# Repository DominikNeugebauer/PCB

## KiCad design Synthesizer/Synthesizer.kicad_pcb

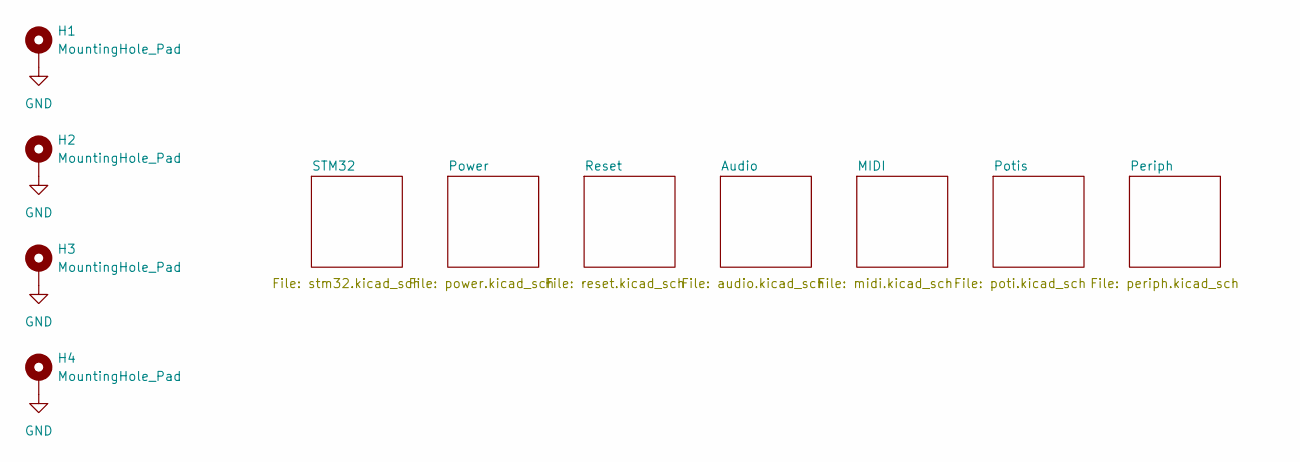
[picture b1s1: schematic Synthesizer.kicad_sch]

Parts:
H1, H2, H3, H4: MountingHole_Pad; MountingHole_5.3mm_M5_DIN965_Pad

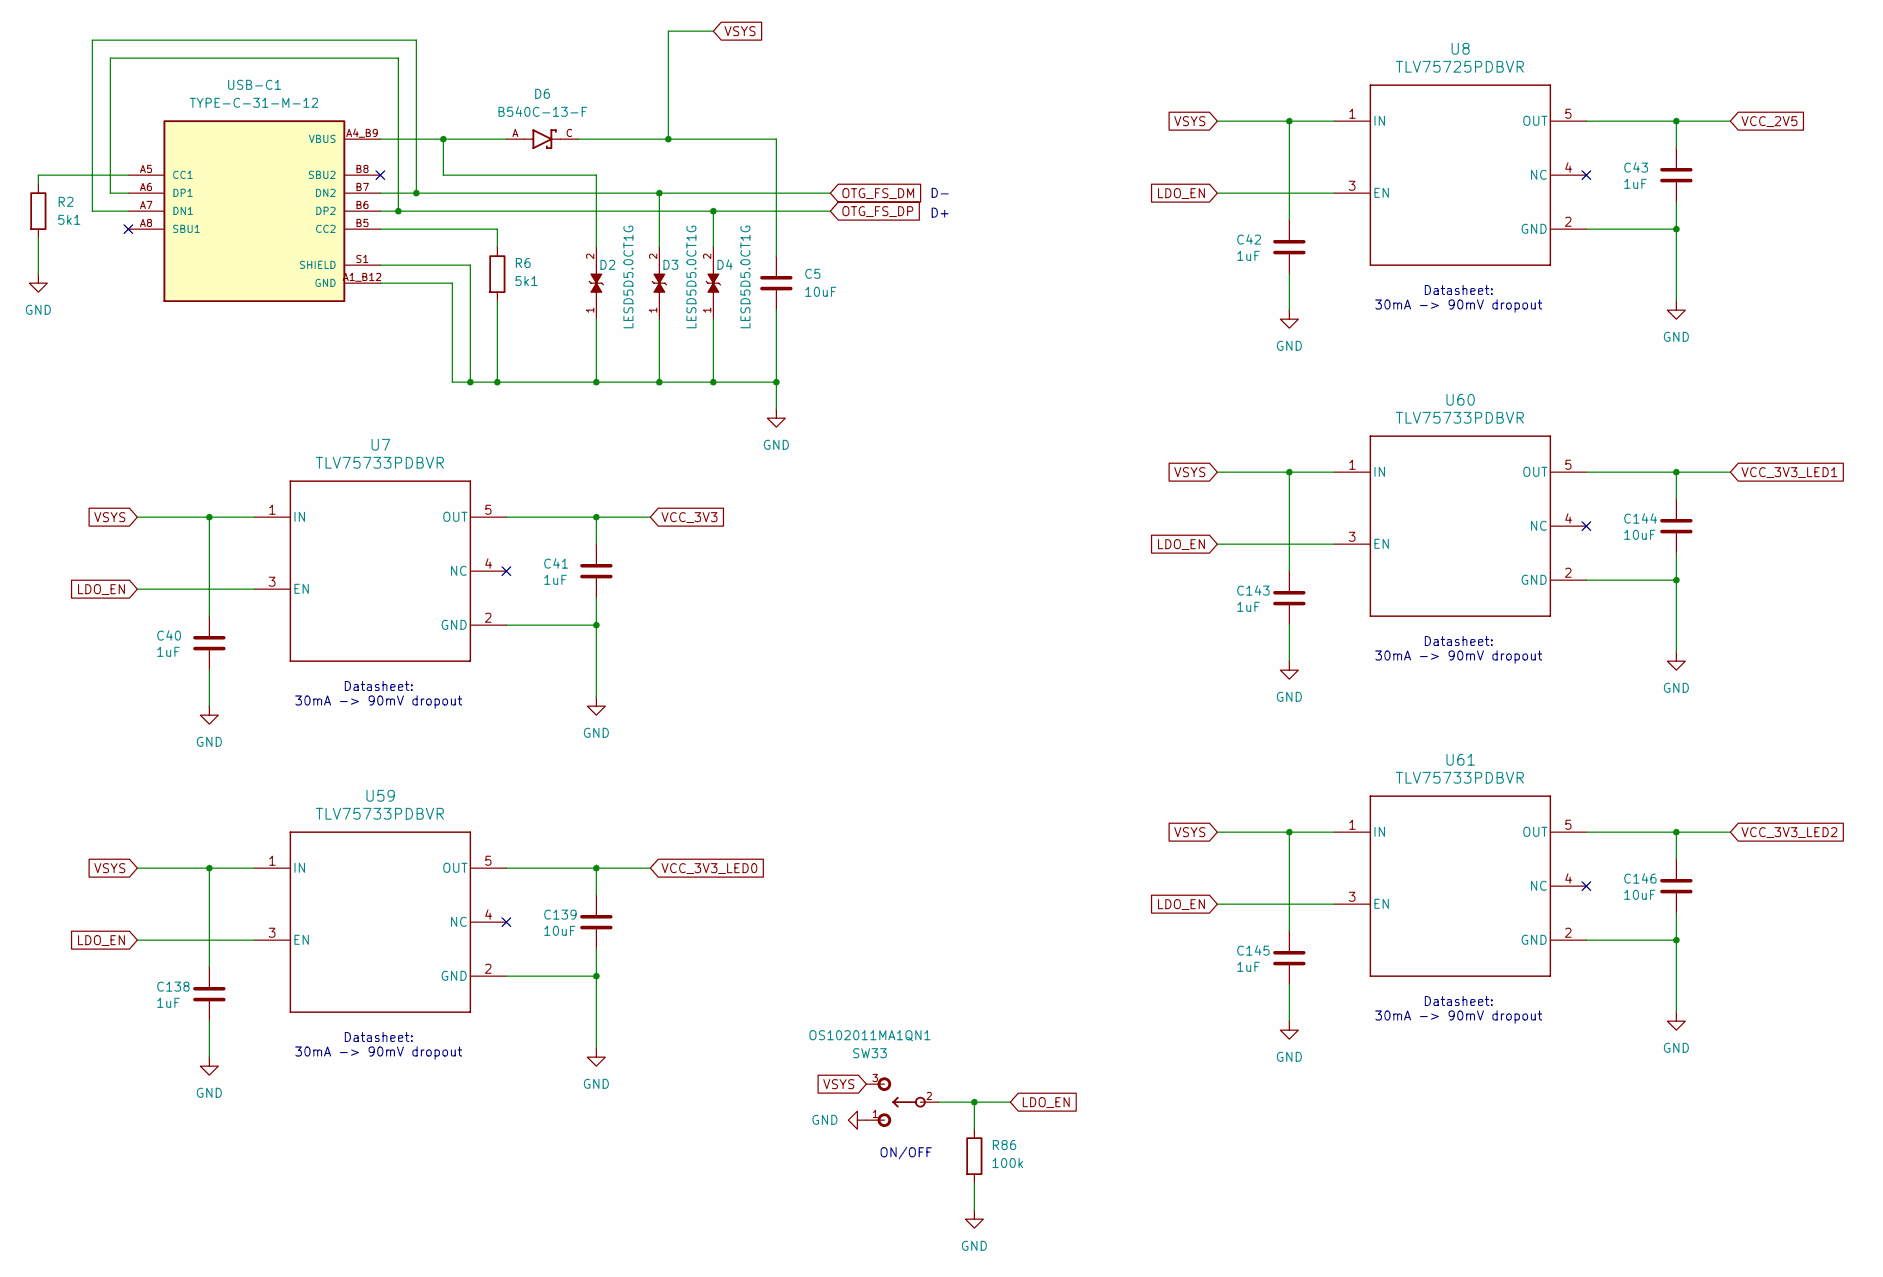
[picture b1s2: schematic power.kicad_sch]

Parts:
C5, C139, C144, C146: 10uF; C_0603_1608Metric
C40, C41, C42, C43, C138, C143, C145: 1uF; C_0603_1608Metric
D2, D3, D4: LESD5D5.0CT1G; TVS_LESD5D5.0CT1G; PARTREV O
D6: B540C-13-F; MPN B540C-13-F
R2, R6: 5k1; R_0603_1608Metric
R86: 100k; R_0603_1608Metric
SW33: OS102011MA1QN1; SWITCH_OS102011MA1QN1_SWITCH_11MA1QN1; MANUFACTURER_PART_NUMBER OS102011MA1QN1
U7, U59, U60, U61: TLV75733PDBVR; SOT-23-5
U8: TLV75725PDBVR; SOT-23-5
USB-C1: TYPE-C-31-M-12; USBC_HRO_TYPE-C-31-M-12; PARTREV 2020.12.08

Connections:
LDO_EN: R86.1, SW33.2, U7.3 (EN), U8.3 (EN), U59.3 (EN), U60.3 (EN), U61.3 (EN)
unnamed: R2.1, USB-C1.A5 (CC1)
unnamed: R6.1, USB-C1.B5 (CC2)
OTG_FS_DM: D3.2, USB-C1.A7 (DN1), USB-C1.B7 (DN2); also elsewhere on the board
OTG_FS_DP: D4.2, USB-C1.A6 (DP1), USB-C1.B6 (DP2); also elsewhere on the board
VBUS: D2.2, D6.A, USB-C1.A4_B9 (VBUS), USB-C1.B4_A9 (VBUS)
VCC_2V5: C43.1, U8.5 (OUT); also elsewhere on the board
VCC_3V3: C41.1, U7.5 (OUT); also elsewhere on the board
VCC_3V3_LED0: C139.1, U59.5 (OUT); also elsewhere on the board
VCC_3V3_LED1: C144.1, U60.5 (OUT); also elsewhere on the board
VCC_3V3_LED2: C146.1, U61.5 (OUT); also elsewhere on the board
VSYS: C5.1, C40.1, C42.1, C138.1, C143.1, C145.1, D6.C, SW33.3, U7.1 (IN), U8.1 (IN), U59.1 (IN), U60.1 (IN), U61.1 (IN)

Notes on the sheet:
Datasheet: 30mA -> 90mV dropout
ON/OFF

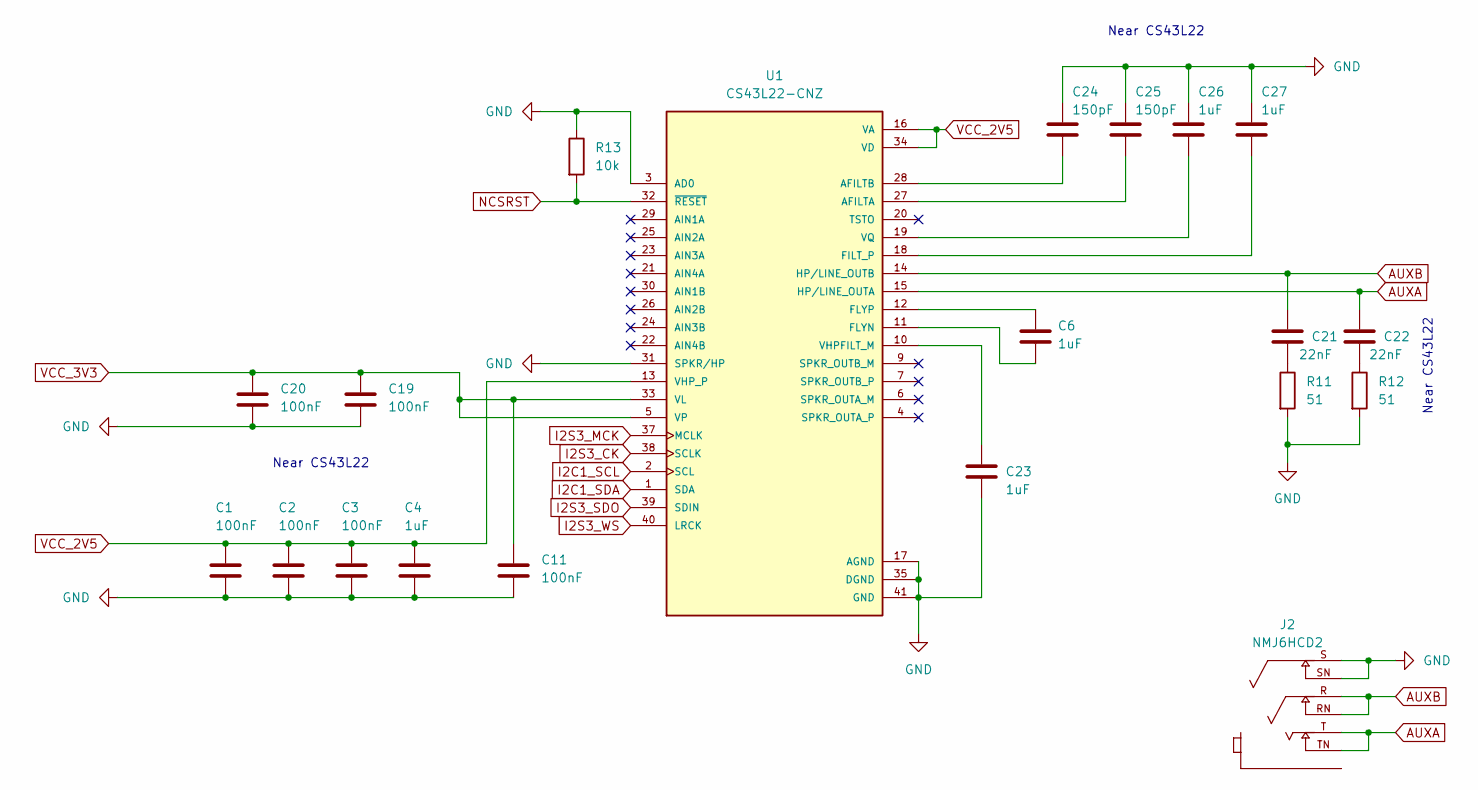
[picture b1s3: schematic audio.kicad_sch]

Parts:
C1, C2, C3, C11, C19, C20: 100nF; C_0603_1608Metric
C4, C6, C23, C26, C27: 1uF; C_0603_1608Metric
C21, C22: 22nF; C_0603_1608Metric
C24, C25: 150pF; C_0603_1608Metric
J2: NMJ6HCD2; AUXBIG_NEUTRIK_NMJ6HCD2; PARTREV 26.02.2021
R11, R12: 51; R_0603_1608Metric
R13: 10k; R_0603_1608Metric
U1: CS43L22-CNZ; CS43L22; PARTREV F2

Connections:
AUXA: C22.1, J2.T, J2.TN, U1.15 (HP/LINE_OUTA)
AUXB: C21.1, J2.R, J2.RN, U1.14 (HP/LINE_OUTB)
I2C1_SCL: U1.2 (SCL); also elsewhere on the board
I2C1_SDA: U1.1 (SDA); also elsewhere on the board
I2S3_CK: U1.38 (SCLK); also elsewhere on the board
I2S3_MCK: U1.37 (MCLK); also elsewhere on the board
I2S3_SDO: U1.39 (SDIN); also elsewhere on the board
I2S3_WS: U1.40 (LRCK); also elsewhere on the board
NCSRST: R13.2, U1.32 (~RESET); also elsewhere on the board
unnamed: C21.2, R11.1
unnamed: C22.2, R12.1
unnamed: C25.2, U1.27 (AFILTA)
unnamed: C24.2, U1.28 (AFILTB)
unnamed: C27.2, U1.18 (FILT_P)
unnamed: C6.2, U1.11 (FLYN)
unnamed: C6.1, U1.12 (FLYP)
unnamed: C23.1, U1.10 (VHPFILT_M)
unnamed: C26.2, U1.19 (VQ)
VCC_2V5: C1.1, C2.1, C3.1, C4.1, U1.13 (VHP_P), U1.16 (VA), U1.34 (VD); also elsewhere on the board
VCC_3V3: C11.1, C19.1, C20.1, U1.5 (VP), U1.8 (VP), U1.33 (VL); also elsewhere on the board

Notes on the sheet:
Near CS43L22

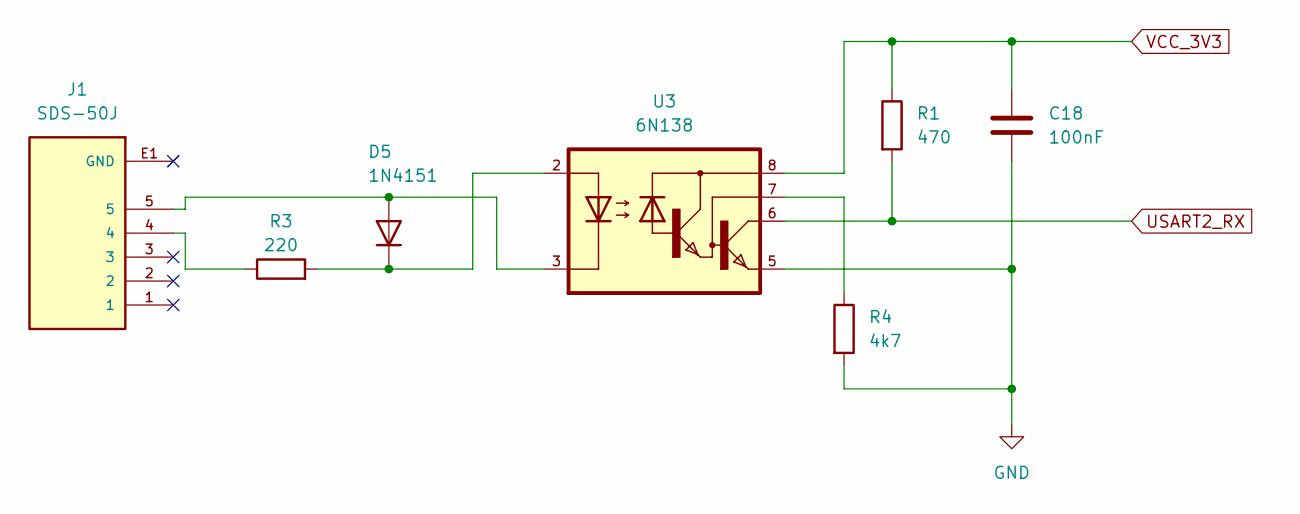
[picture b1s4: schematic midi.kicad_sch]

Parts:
C18: 100nF; C_0603_1608Metric
D5: 1N4151; D_DO-35_SOD27_P7.62mm_Horizontal
J1: SDS-50J; MIDI_CUI_SDS-50J; PARTREV 1.06/02-13-2020
R1: 470; R_0603_1608Metric
R3: 220; R_0603_1608Metric
R4: 4k7; R_0603_1608Metric
U3: 6N138

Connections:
unnamed: D5.2 (A), J1.5, U3.3
unnamed: D5.1 (K), R3.2, U3.2
unnamed: J1.4, R3.1
unnamed: R4.1, U3.7
USART2_RX: R1.2, U3.6; also elsewhere on the board
VCC_3V3: C18.1, R1.1, U3.8; also elsewhere on the board

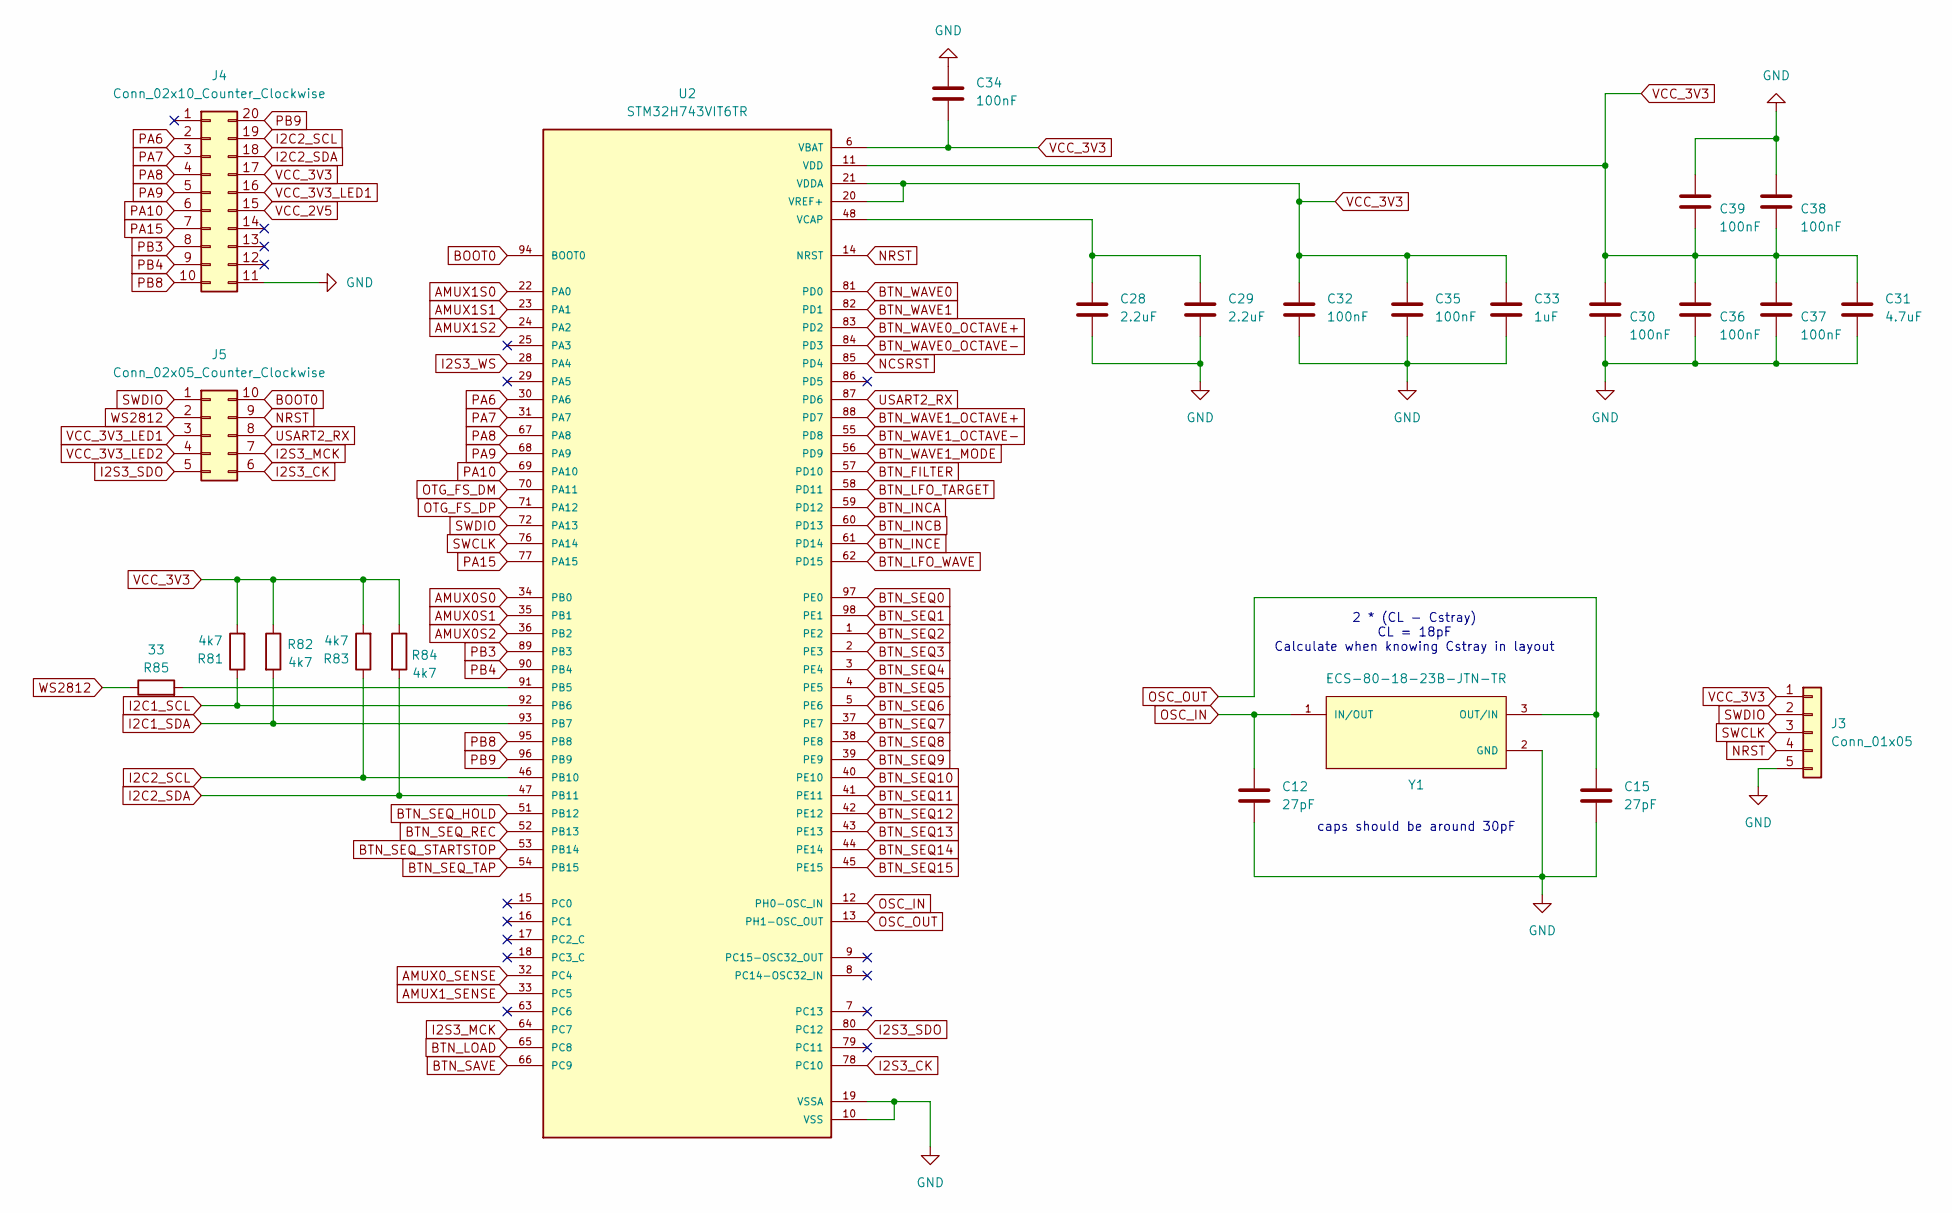
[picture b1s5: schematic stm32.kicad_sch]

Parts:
C12, C15: 27pF; C_0603_1608Metric
C28, C29: 2.2uF; C_0603_1608Metric
C30, C32, C34, C35, C36, C37, C38, C39: 100nF; C_0603_1608Metric
C31: 4.7uF; C_0603_1608Metric
C33: 1uF; C_0603_1608Metric
J3: Conn_01x05; PinHeader_1x05_P2.54mm_Vertical
J4: Conn_02x10_Counter_Clockwise; PinSocket_2x10_P2.54mm_Vertical
J5: Conn_02x05_Counter_Clockwise; PinSocket_2x05_P2.54mm_Vertical
R81, R82, R83, R84: 4k7; R_0603_1608Metric
R85: 33; R_0603_1608Metric
U2: STM32H743VIT6TR; PARTREV 7
Y1: ECS-80-18-23B-JTN-TR; XTAL_ECS-80-18-23B-JTN-TR

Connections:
AMUX0S0: U2.34 (PB0); also elsewhere on the board
AMUX0S1: U2.35 (PB1); also elsewhere on the board
AMUX0S2: U2.36 (PB2); also elsewhere on the board
AMUX0_SENSE: U2.32 (PC4); also elsewhere on the board
AMUX1S0: U2.22 (PA0); also elsewhere on the board
AMUX1S1: U2.23 (PA1); also elsewhere on the board
AMUX1S2: U2.24 (PA2); also elsewhere on the board
AMUX1_SENSE: U2.33 (PC5); also elsewhere on the board
BOOT0: J5.10, U2.94 (BOOT0); also elsewhere on the board
BTN_FILTER: U2.57 (PD10); also elsewhere on the board
BTN_INCA: U2.59 (PD12); also elsewhere on the board
BTN_INCB: U2.60 (PD13); also elsewhere on the board
BTN_INCE: U2.61 (PD14); also elsewhere on the board
BTN_LFO_TARGET: U2.58 (PD11); also elsewhere on the board
BTN_LFO_WAVE: U2.62 (PD15); also elsewhere on the board
BTN_LOAD: U2.65 (PC8); also elsewhere on the board
BTN_SAVE: U2.66 (PC9); also elsewhere on the board
BTN_SEQ0: U2.97 (PE0); also elsewhere on the board
BTN_SEQ1: U2.98 (PE1); also elsewhere on the board
BTN_SEQ2: U2.1 (PE2); also elsewhere on the board
BTN_SEQ3: U2.2 (PE3); also elsewhere on the board
BTN_SEQ4: U2.3 (PE4); also elsewhere on the board
BTN_SEQ5: U2.4 (PE5); also elsewhere on the board
BTN_SEQ6: U2.5 (PE6); also elsewhere on the board
BTN_SEQ7: U2.37 (PE7); also elsewhere on the board
BTN_SEQ8: U2.38 (PE8); also elsewhere on the board
BTN_SEQ9: U2.39 (PE9); also elsewhere on the board
BTN_SEQ10: U2.40 (PE10); also elsewhere on the board
BTN_SEQ11: U2.41 (PE11); also elsewhere on the board
BTN_SEQ12: U2.42 (PE12); also elsewhere on the board
BTN_SEQ13: U2.43 (PE13); also elsewhere on the board
BTN_SEQ14: U2.44 (PE14); also elsewhere on the board
BTN_SEQ15: U2.45 (PE15); also elsewhere on the board
BTN_SEQ_HOLD: U2.51 (PB12); also elsewhere on the board
BTN_SEQ_REC: U2.52 (PB13); also elsewhere on the board
BTN_SEQ_STARTSTOP: U2.53 (PB14); also elsewhere on the board
BTN_SEQ_TAP: U2.54 (PB15); also elsewhere on the board
BTN_WAVE0: U2.81 (PD0); also elsewhere on the board
BTN_WAVE0_OCTAVE+: U2.83 (PD2); also elsewhere on the board
BTN_WAVE0_OCTAVE-: U2.84 (PD3); also elsewhere on the board
BTN_WAVE1: U2.82 (PD1); also elsewhere on the board
BTN_WAVE1_MODE: U2.56 (PD9); also elsewhere on the board
BTN_WAVE1_OCTAVE+: U2.88 (PD7); also elsewhere on the board
BTN_WAVE1_OCTAVE-: U2.55 (PD8); also elsewhere on the board
I2C1_SCL: R81.1, U2.92 (PB6); also elsewhere on the board
I2C1_SDA: R82.2, U2.93 (PB7); also elsewhere on the board
I2C2_SCL: J4.19, R83.1, U2.46 (PB10)
I2C2_SDA: J4.18, R84.2, U2.47 (PB11)
I2S3_CK: J5.6, U2.78 (PC10); also elsewhere on the board
I2S3_MCK: J5.7, U2.64 (PC7); also elsewhere on the board
I2S3_SDO: J5.5, U2.80 (PC12); also elsewhere on the board
I2S3_WS: U2.28 (PA4); also elsewhere on the board
NCSRST: U2.85 (PD4); also elsewhere on the board
NRST: J3.4, J5.9, U2.14 (NRST); also elsewhere on the board
unnamed: R85.2, U2.91 (PB5)
OSC_IN: C12.1, U2.12 (PH0-OSC_IN), Y1.1 (IN/OUT)
OSC_OUT: C15.1, U2.13 (PH1-OSC_OUT), Y1.3 (OUT/IN)
OTG_FS_DM: U2.70 (PA11); also elsewhere on the board
OTG_FS_DP: U2.71 (PA12); also elsewhere on the board
PA6: J4.2, U2.30 (PA6)
PA7: J4.3, U2.31 (PA7)
PA8: J4.4, U2.67 (PA8)
PA9: J4.5, U2.68 (PA9)
PA10: J4.6, U2.69 (PA10)
PA15: J4.7, U2.77 (PA15)
PB3: J4.8, U2.89 (PB3)
PB4: J4.9, U2.90 (PB4)
PB8: J4.10, U2.95 (PB8)
PB9: J4.20, U2.96 (PB9)
SWCLK: J3.3, U2.76 (PA14)
SWDIO: J3.2, J5.1, U2.72 (PA13)
USART2_RX: J5.8, U2.87 (PD6); also elsewhere on the board
VCAP: C28.1, C29.1, U2.48 (VCAP), U2.73 (VCAP)
VCC_2V5: J4.15; also elsewhere on the board
VCC_3V3: C30.1, C31.1, C32.1, C33.1, C34.2, C35.1, C36.1, C37.1, C38.2, C39.2, J3.1, J4.17, R81.2, R82.1, R83.2, R84.1, U2.6 (VBAT), U2.11 (VDD), U2.20 (VREF+), U2.21 (VDDA), U2.27 (VDD), U2.50 (VDD), U2.75 (VDD), U2.100 (VDD); also elsewhere on the board
VCC_3V3_LED1: J4.16, J5.3; also elsewhere on the board
VCC_3V3_LED2: J5.4; also elsewhere on the board
WS2812: J5.2, R85.1; also elsewhere on the board

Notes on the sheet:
caps should be around 30pF
2 * (CL - Cstray) CL = 18pF Calculate when knowing Cstray in layout

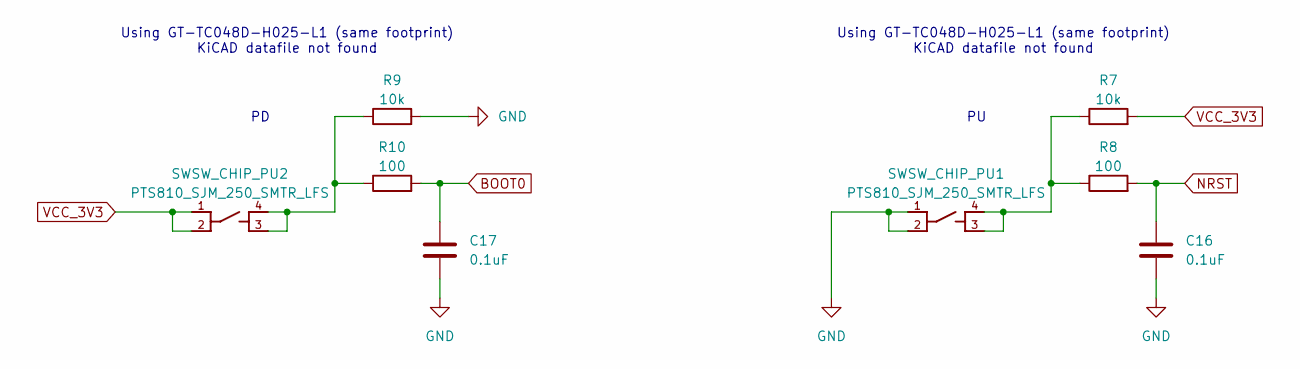
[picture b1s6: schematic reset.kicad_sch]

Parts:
C16, C17: 0.1uF; C_0603_1608Metric
R7, R9: 10k; R_0603_1608Metric
R8, R10: 100; R_0603_1608Metric
SWSW_CHIP_PU1, SWSW_CHIP_PU2: PTS810_SJM_250_SMTR_LFS; SW_PTS810_SJM_250_SMTR_LFS

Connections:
BOOT0: C17.1, R10.2; also elsewhere on the board
NRST: C16.1, R8.2; also elsewhere on the board
unnamed: R7.1, R8.1, SWSW_CHIP_PU1.3, SWSW_CHIP_PU1.4
unnamed: R9.1, R10.1, SWSW_CHIP_PU2.3, SWSW_CHIP_PU2.4
VCC_3V3: R7.2, SWSW_CHIP_PU2.1, SWSW_CHIP_PU2.2; also elsewhere on the board

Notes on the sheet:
Using GT-TC048D-H025-L1 (same footprint) KiCAD datafile not found

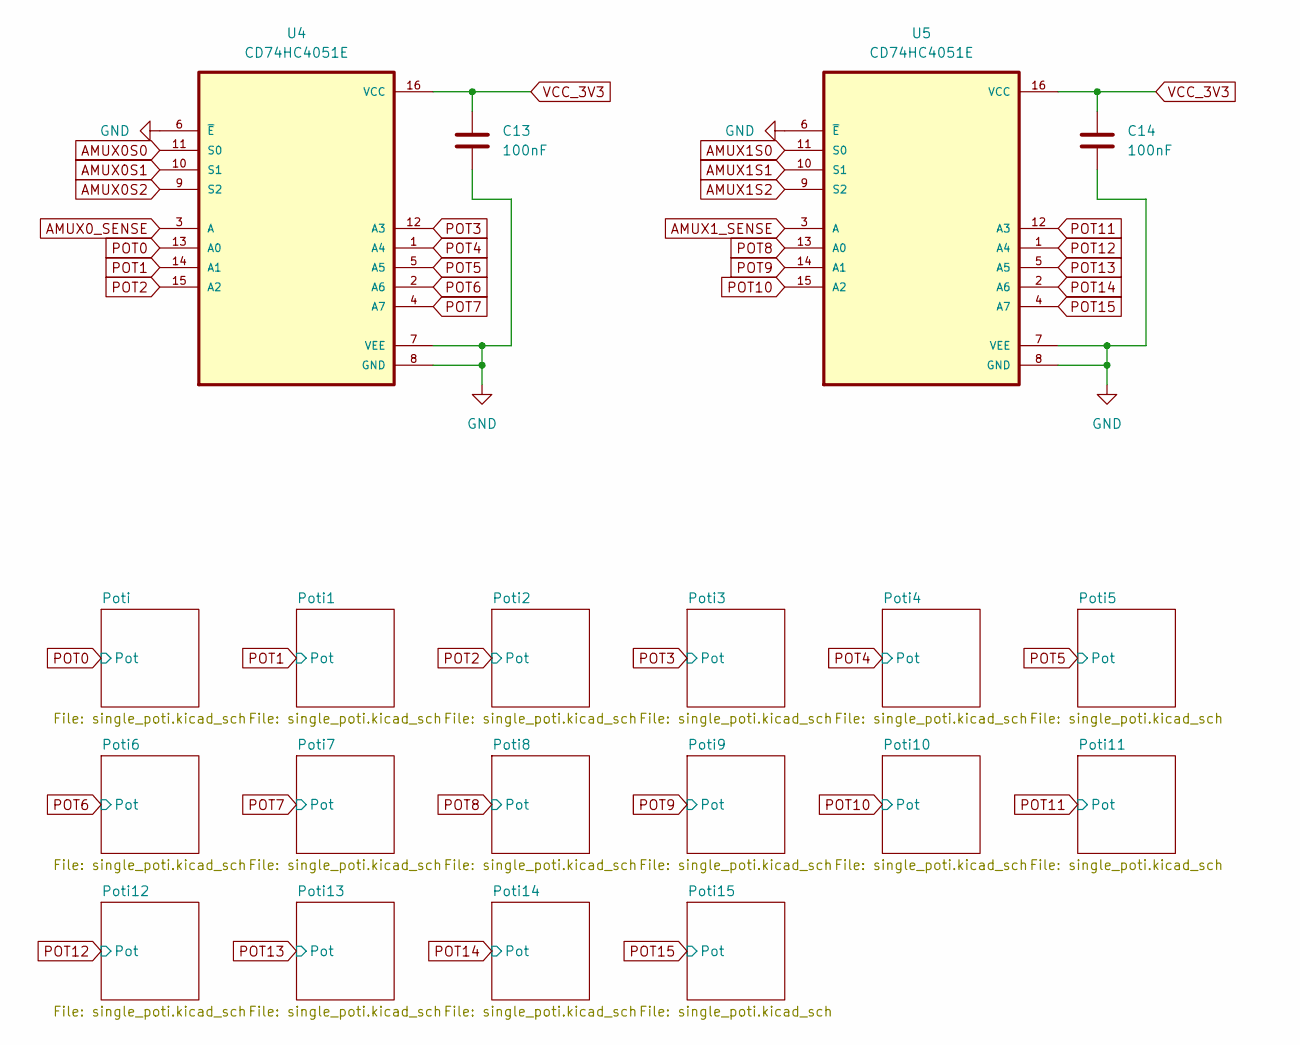
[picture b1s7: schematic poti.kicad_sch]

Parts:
C13, C14: 100nF; C_0603_1608Metric
U4, U5: CD74HC4051E

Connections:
AMUX0S0: U4.11 (S0); also elsewhere on the board
AMUX0S1: U4.10 (S1); also elsewhere on the board
AMUX0S2: U4.9 (S2); also elsewhere on the board
AMUX0_SENSE: U4.3 (A); also elsewhere on the board
AMUX1S0: U5.11 (S0); also elsewhere on the board
AMUX1S1: U5.10 (S1); also elsewhere on the board
AMUX1S2: U5.9 (S2); also elsewhere on the board
AMUX1_SENSE: U5.3 (A); also elsewhere on the board
POT0: U4.13 (A0); also elsewhere on the board
POT1: U4.14 (A1); also elsewhere on the board
POT2: U4.15 (A2); also elsewhere on the board
POT3: U4.12 (A3); also elsewhere on the board
POT4: U4.1 (A4); also elsewhere on the board
POT5: U4.5 (A5); also elsewhere on the board
POT6: U4.2 (A6); also elsewhere on the board
POT7: U4.4 (A7); also elsewhere on the board
POT8: U5.13 (A0); also elsewhere on the board
POT9: U5.14 (A1); also elsewhere on the board
POT10: U5.15 (A2); also elsewhere on the board
POT11: U5.12 (A3); also elsewhere on the board
POT12: U5.1 (A4); also elsewhere on the board
POT13: U5.5 (A5); also elsewhere on the board
POT14: U5.2 (A6); also elsewhere on the board
POT15: U5.4 (A7); also elsewhere on the board
VCC_3V3: C13.1, C14.1, U4.16 (VCC), U5.16 (VCC); also elsewhere on the board

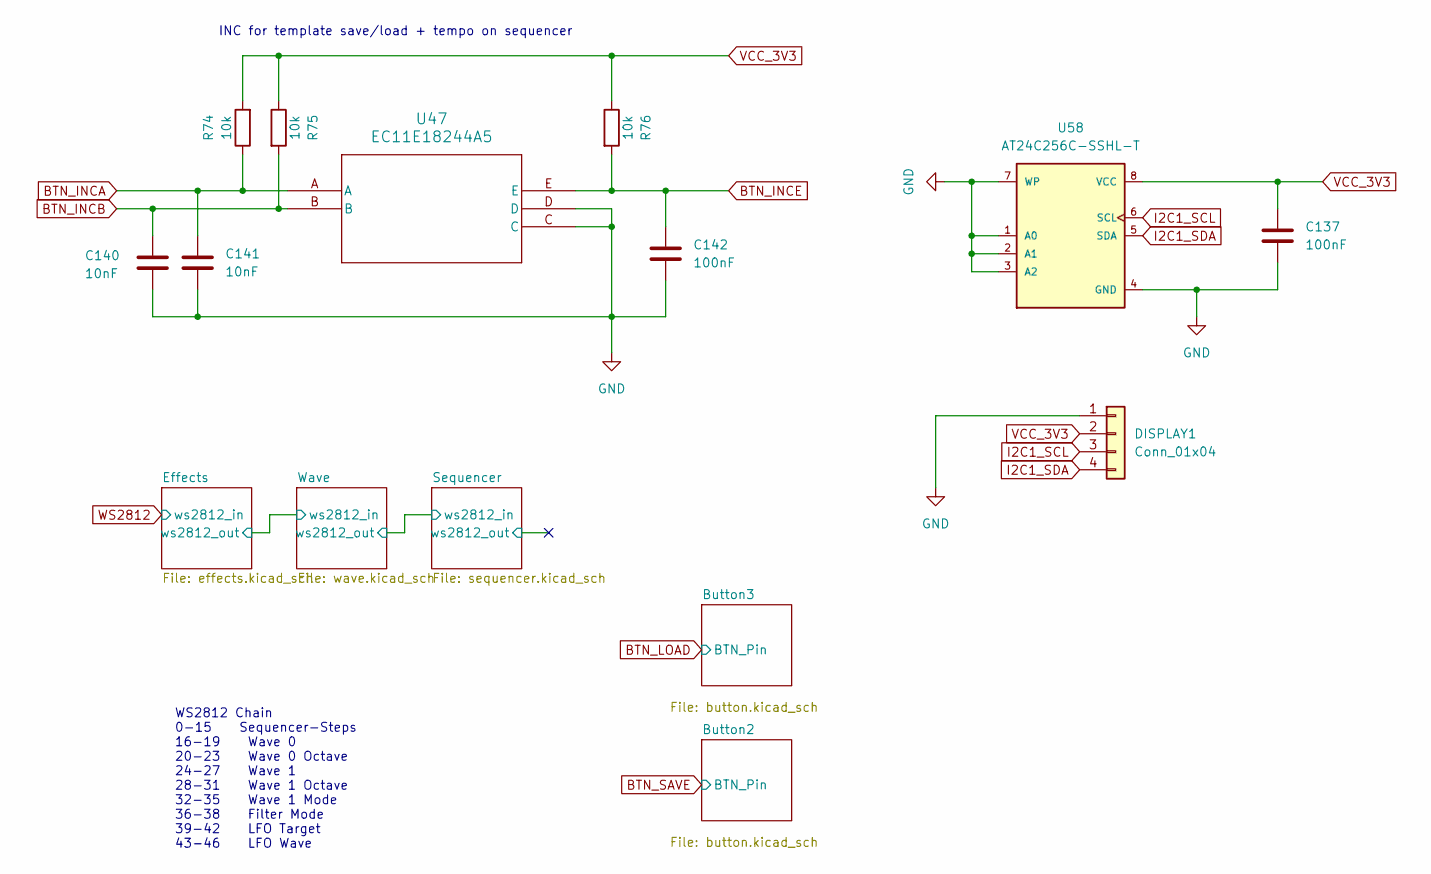
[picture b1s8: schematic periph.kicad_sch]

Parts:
C137, C142: 100nF; C_0603_1608Metric
C140, C141: 10nF; C_0603_1608Metric
DISPLAY1: Conn_01x04; PinHeader_1x04_P2.54mm_Vertical
R74, R75, R76: 10k; R_0603_1608Metric
U47: EC11E18244A5; EC11E18244A5_ALPS
U58: AT24C256C-SSHL-T

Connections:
BTN_INCA: C141.1, R74.1, U47.A; also elsewhere on the board
BTN_INCB: C140.1, R75.2, U47.B; also elsewhere on the board
BTN_INCE: C142.1, R76.2, U47.E; also elsewhere on the board
I2C1_SCL: DISPLAY1.3, U58.6 (SCL); also elsewhere on the board
I2C1_SDA: DISPLAY1.4, U58.5 (SDA); also elsewhere on the board
VCC_3V3: C137.1, DISPLAY1.2, R74.2, R75.1, R76.1, U58.8 (VCC); also elsewhere on the board

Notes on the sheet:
INC for template save/load + tempo on sequencer
WS2812 Chain 0-15 Sequencer-Steps 16-19 Wave 0 20-23 Wave 0 Octave 24-27 Wave 1 28-31 Wave 1 Octave 32-35 Wave 1 Mode 36-38 Filter Mode 39-42 LFO Target 43-46 LFO Wave

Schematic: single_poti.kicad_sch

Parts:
C7: 100nF; C_0603_1608Metric
RV1: R_Potentiometer; Potentiometer_RV16106NO_A-5419_Vertical

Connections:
POT0: C7.2, RV1.2; also elsewhere on the board
VCC_3V3: RV1.3; also elsewhere on the board

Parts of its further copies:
C8, C9, C10, C44, C45, C46, C47, C48, C49, C50, C51, C52, C53, C54, C55: 100nF; C_0603_1608Metric
RV2, RV3, RV4, RV5, RV6, RV7, RV8, RV9, RV10, RV11, RV12, RV13, RV14, RV15, RV16: R_Potentiometer; Potentiometer_RV16106NO_A-5419_Vertical

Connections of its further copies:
POT1: C8.2, RV2.2; also elsewhere on the board
POT2: C9.2, RV3.2; also elsewhere on the board
POT3: C10.2, RV4.2; also elsewhere on the board
POT4: C44.2, RV5.2; also elsewhere on the board
POT5: C45.2, RV6.2; also elsewhere on the board
POT6: C46.2, RV7.2; also elsewhere on the board
POT7: C47.2, RV8.2; also elsewhere on the board
POT8: C48.2, RV9.2; also elsewhere on the board
POT9: C49.2, RV10.2; also elsewhere on the board
POT10: C50.2, RV11.2; also elsewhere on the board
POT11: C51.2, RV12.2; also elsewhere on the board
POT12: C52.2, RV13.2; also elsewhere on the board
POT13: C53.2, RV14.2; also elsewhere on the board
POT14: C54.2, RV15.2; also elsewhere on the board
POT15: C55.2, RV16.2; also elsewhere on the board
VCC_3V3: RV2.3, RV3.3, RV4.3, RV5.3, RV6.3, RV7.3, RV8.3, RV9.3, RV10.3, RV11.3, RV12.3, RV13.3, RV14.3, RV15.3, RV16.3; also elsewhere on the board

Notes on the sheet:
Near ADC

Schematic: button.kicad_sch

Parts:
C56: 0.1uF; C_0603_1608Metric
R14: 10k; R_0603_1608Metric
R15: 100; R_0603_1608Metric
SW25: SW_Push; SW_Cherry_MX_1.00u_PCB

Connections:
BTN_WAVE0: C56.1, R15.2; also elsewhere on the board
unnamed: R14.1, R15.1, SW25.2
VCC_3V3: R14.2; also elsewhere on the board

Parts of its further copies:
C61, C66, C67, C68, C69, C70, C71, C72, C73, C74, C75, C76, C77, C78, C79, C80, C81, C98, C99, C100, C101, C106, C111, C112, C113, C114, C122, C123, C124, C129, C134: 0.1uF; C_0603_1608Metric
R16, R18, R20, R22, R24, R26, R28, R30, R32, R34, R36, R38, R40, R42, R44, R46, R48, R50, R52, R54, R56, R58, R60, R62, R64, R66, R68, R70, R72, R77, R79: 10k; R_0603_1608Metric
R17, R19, R21, R23, R25, R27, R29, R31, R33, R35, R37, R39, R41, R43, R45, R47, R49, R51, R53, R55, R57, R59, R61, R63, R65, R67, R69, R71, R73, R78, R80: 100; R_0603_1608Metric
SW1, SW2, SW3, SW4, SW5, SW6, SW7, SW8, SW9, SW10, SW11, SW12, SW13, SW14, SW15, SW16, SW17, SW18, SW19, SW20, SW21, SW22, SW23, SW24, SW26, SW27, SW28, SW29, SW30, SW31, SW32: SW_Push; SW_Cherry_MX_1.00u_PCB

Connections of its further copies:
BTN_FILTER: C123.1, R69.2; also elsewhere on the board
BTN_LFO_TARGET: C124.1, R71.2; also elsewhere on the board
BTN_LFO_WAVE: C129.1, R73.2; also elsewhere on the board
BTN_LOAD: C134.1, R80.2; also elsewhere on the board
BTN_SAVE: C122.1, R78.2; also elsewhere on the board
BTN_SEQ0: C66.1, R19.2; also elsewhere on the board
BTN_SEQ1: C67.1, R21.2; also elsewhere on the board
BTN_SEQ2: C68.1, R23.2; also elsewhere on the board
BTN_SEQ3: C69.1, R25.2; also elsewhere on the board
BTN_SEQ4: C70.1, R27.2; also elsewhere on the board
BTN_SEQ5: C71.1, R29.2; also elsewhere on the board
BTN_SEQ6: C72.1, R31.2; also elsewhere on the board
BTN_SEQ7: C73.1, R33.2; also elsewhere on the board
BTN_SEQ8: C74.1, R35.2; also elsewhere on the board
BTN_SEQ9: C75.1, R37.2; also elsewhere on the board
BTN_SEQ10: C76.1, R39.2; also elsewhere on the board
BTN_SEQ11: C77.1, R41.2; also elsewhere on the board
BTN_SEQ12: C78.1, R43.2; also elsewhere on the board
BTN_SEQ13: C79.1, R45.2; also elsewhere on the board
BTN_SEQ14: C80.1, R47.2; also elsewhere on the board
BTN_SEQ15: C81.1, R49.2; also elsewhere on the board
BTN_SEQ_HOLD: C100.1, R55.2; also elsewhere on the board
BTN_SEQ_REC: C98.1, R51.2; also elsewhere on the board
BTN_SEQ_STARTSTOP: C99.1, R53.2; also elsewhere on the board
BTN_SEQ_TAP: C113.1, R65.2; also elsewhere on the board
BTN_WAVE0_OCTAVE+: C101.1, R57.2; also elsewhere on the board
BTN_WAVE0_OCTAVE-: C112.1, R63.2; also elsewhere on the board
BTN_WAVE1: C61.1, R17.2; also elsewhere on the board
BTN_WAVE1_MODE: C114.1, R67.2; also elsewhere on the board
BTN_WAVE1_OCTAVE+: C106.1, R59.2; also elsewhere on the board
BTN_WAVE1_OCTAVE-: C111.1, R61.2; also elsewhere on the board
unnamed: R16.1, R17.1, SW1.2
unnamed: R18.1, R19.1, SW2.2
unnamed: R20.1, R21.1, SW3.2
unnamed: R22.1, R23.1, SW4.2
unnamed: R24.1, R25.1, SW5.2
unnamed: R26.1, R27.1, SW6.2
unnamed: R28.1, R29.1, SW7.2
unnamed: R30.1, R31.1, SW8.2
unnamed: R32.1, R33.1, SW9.2
unnamed: R34.1, R35.1, SW10.2
unnamed: R36.1, R37.1, SW11.2
unnamed: R38.1, R39.1, SW12.2
unnamed: R40.1, R41.1, SW13.2
unnamed: R42.1, R43.1, SW14.2
unnamed: R44.1, R45.1, SW15.2
unnamed: R46.1, R47.1, SW16.2
unnamed: R48.1, R49.1, SW17.2
unnamed: R50.1, R51.1, SW18.2
unnamed: R52.1, R53.1, SW19.2
unnamed: R54.1, R55.1, SW20.2
unnamed: R56.1, R57.1, SW21.2
unnamed: R58.1, R59.1, SW22.2
unnamed: R60.1, R61.1, SW23.2
unnamed: R62.1, R63.1, SW24.2
unnamed: R64.1, R65.1, SW26.2
unnamed: R66.1, R67.1, SW27.2
unnamed: R68.1, R69.1, SW28.2
unnamed: R70.1, R71.1, SW29.2
unnamed: R72.1, R73.1, SW30.2
unnamed: R77.1, R78.1, SW31.2
unnamed: R79.1, R80.1, SW32.2
VCC_3V3: R16.2, R18.2, R20.2, R22.2, R24.2, R26.2, R28.2, R30.2, R32.2, R34.2, R36.2, R38.2, R40.2, R42.2, R44.2, R46.2, R48.2, R50.2, R52.2, R54.2, R56.2, R58.2, R60.2, R62.2, R64.2, R66.2, R68.2, R70.2, R72.2, R77.2, R79.2; also elsewhere on the board

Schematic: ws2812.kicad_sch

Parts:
C147: 100nF; C_0603_1608Metric
U62: WS2812B; WS2812B_WDS

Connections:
/Periph/Sequencer/WS28135/out: U62.4 (DIN); also elsewhere on the board
/Periph/Sequencer/WS28143/IN: U62.2 (DOUT); also elsewhere on the board
VCC_3V3_LED1: C147.1, U62.1 (VDD); also elsewhere on the board

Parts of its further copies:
C57, C58, C59, C60, C62, C63, C64, C65, C82, C83, C84, C85, C86, C87, C88, C89, C90, C91, C92, C93, C94, C95, C96, C97, C102, C103, C104, C105, C107, C108, C109, C110, C115, C116, C117, C118, C119, C120, C121, C125, C126, C127, C128, C130, C131, C132, C133: 100nF; C_0603_1608Metric
U6, U9, U10, U11, U12, U13, U14, U15, U16, U17, U18, U19, U20, U21, U22, U23, U24, U25, U26, U27, U28, U29, U30, U31, U32, U33, U34, U35, U36, U37, U38, U39, U40, U41, U42, U43, U44, U45, U46, U48, U49, U50, U51, U52, U53, U54, U55: WS2812B; WS2812B_WDS

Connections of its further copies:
/Periph/Effects/WS28128/IN: U44.4 (DIN)
/Periph/Effects/WS28128/out: U44.2 (DOUT), U45.4 (DIN)
/Periph/Effects/WS28129/out: U45.2 (DOUT), U46.4 (DIN)
/Periph/Effects/WS28132/IN: U48.4 (DIN), U55.2 (DOUT)
/Periph/Effects/WS28132/out: U48.2 (DOUT), U49.4 (DIN)
/Periph/Effects/WS28133/out: U49.2 (DOUT), U50.4 (DIN)
/Periph/Effects/WS28134/out: U50.2 (DOUT), U51.4 (DIN)
/Periph/Effects/WS28135/out: U51.2 (DOUT)
/Periph/Effects/WS28136/out: U52.2 (DOUT), U53.4 (DIN)
/Periph/Effects/WS28137/out: U53.2 (DOUT), U54.4 (DIN)
/Periph/Effects/WS28138/out: U54.2 (DOUT), U55.4 (DIN)
/Periph/Effects/ws2812_out: U40.4 (DIN), U46.2 (DOUT)
/Periph/Sequencer/WS28128/out: U9.2 (DOUT), U17.4 (DIN)
/Periph/Sequencer/WS28129/out: U17.2 (DOUT), U18.4 (DIN)
/Periph/Sequencer/WS28130/out: U18.2 (DOUT), U19.4 (DIN)
/Periph/Sequencer/WS28131/out: U19.2 (DOUT), U20.4 (DIN)
/Periph/Sequencer/WS28132/out: U20.2 (DOUT), U21.4 (DIN)
/Periph/Sequencer/WS28133/out: U21.2 (DOUT), U22.4 (DIN)
/Periph/Sequencer/WS28134/out: U22.2 (DOUT), U23.4 (DIN)
/Periph/Sequencer/WS28135/out: U23.2 (DOUT); also elsewhere on the board
/Periph/Sequencer/WS28136/IN: U24.4 (DIN), U25.2 (DOUT)
/Periph/Sequencer/WS28137/IN: U25.4 (DIN), U26.2 (DOUT)
/Periph/Sequencer/WS28138/IN: U26.4 (DIN), U27.2 (DOUT)
/Periph/Sequencer/WS28139/IN: U27.4 (DIN), U28.2 (DOUT)
/Periph/Sequencer/WS28140/IN: U28.4 (DIN), U29.2 (DOUT)
/Periph/Sequencer/WS28141/IN: U29.4 (DIN), U30.2 (DOUT)
/Periph/Sequencer/WS28142/IN: U30.4 (DIN), U31.2 (DOUT)
/Periph/Sequencer/WS28143/IN: U31.4 (DIN); also elsewhere on the board
/Periph/Sequencer/ws2812_in: U9.4 (DIN), U35.2 (DOUT)
/Periph/Sequencer/ws2812_out: U24.2 (DOUT)
/Periph/Wave/WS28120/IN: U6.4 (DIN), U39.2 (DOUT)
/Periph/Wave/WS28120/out: U6.2 (DOUT), U10.4 (DIN)
/Periph/Wave/WS28121/out: U10.2 (DOUT), U11.4 (DIN)
/Periph/Wave/WS28122/out: U11.2 (DOUT), U12.4 (DIN)
/Periph/Wave/WS28123/out: U12.2 (DOUT), U32.4 (DIN)
/Periph/Wave/WS28124/IN: U13.4 (DIN), U43.2 (DOUT)
/Periph/Wave/WS28124/out: U13.2 (DOUT), U14.4 (DIN)
/Periph/Wave/WS28125/out: U14.2 (DOUT), U15.4 (DIN)
/Periph/Wave/WS28126/out: U15.2 (DOUT), U16.4 (DIN)
/Periph/Wave/WS28127/out: U16.2 (DOUT), U36.4 (DIN)
/Periph/Wave/WS28128/out: U40.2 (DOUT), U41.4 (DIN)
/Periph/Wave/WS28129/out: U41.2 (DOUT), U42.4 (DIN)
/Periph/Wave/WS28130/out: U42.2 (DOUT), U43.4 (DIN)
/Periph/Wave/WS28144/out: U32.2 (DOUT), U33.4 (DIN)
/Periph/Wave/WS28145/out: U33.2 (DOUT), U34.4 (DIN)
/Periph/Wave/WS28146/out: U34.2 (DOUT), U35.4 (DIN)
/Periph/Wave/WS28148/out: U36.2 (DOUT), U37.4 (DIN)
/Periph/Wave/WS28149/out: U37.2 (DOUT), U38.4 (DIN)
/Periph/Wave/WS28150/out: U38.2 (DOUT), U39.4 (DIN)
VCC_3V3_LED0: C115.1, C116.1, C117.1, C118.1, C119.1, C120.1, C121.1, C125.1, C126.1, C127.1, C128.1, C130.1, C131.1, C132.1, C133.1, U40.1 (VDD), U41.1 (VDD), U42.1 (VDD), U43.1 (VDD), U44.1 (VDD), U45.1 (VDD), U46.1 (VDD), U48.1 (VDD), U49.1 (VDD), U50.1 (VDD), U51.1 (VDD), U52.1 (VDD), U53.1 (VDD), U54.1 (VDD), U55.1 (VDD); also elsewhere on the board
VCC_3V3_LED1: C82.1, C83.1, C84.1, C85.1, C86.1, C87.1, C88.1, C89.1, C90.1, C91.1, C92.1, C93.1, C94.1, C95.1, C96.1, C97.1, U9.1 (VDD), U17.1 (VDD), U18.1 (VDD), U19.1 (VDD), U20.1 (VDD), U21.1 (VDD), U22.1 (VDD), U23.1 (VDD), U24.1 (VDD), U25.1 (VDD), U26.1 (VDD), U27.1 (VDD), U28.1 (VDD), U29.1 (VDD), U30.1 (VDD), U31.1 (VDD); also elsewhere on the board
VCC_3V3_LED2: C57.1, C58.1, C59.1, C60.1, C62.1, C63.1, C64.1, C65.1, C102.1, C103.1, C104.1, C105.1, C107.1, C108.1, C109.1, C110.1, U6.1 (VDD), U10.1 (VDD), U11.1 (VDD), U12.1 (VDD), U13.1 (VDD), U14.1 (VDD), U15.1 (VDD), U16.1 (VDD), U32.1 (VDD), U33.1 (VDD), U34.1 (VDD), U35.1 (VDD), U36.1 (VDD), U37.1 (VDD), U38.1 (VDD), U39.1 (VDD); also elsewhere on the board
WS2812: U52.4 (DIN); also elsewhere on the board

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

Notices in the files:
parts and their libraries:
COPYRIGHT: Copyright (C) 2024 Ultra Librarian. All rights reserved.
